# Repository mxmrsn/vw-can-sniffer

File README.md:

# VW CAN Sniffer

A home-built diagnostic interface for an MK7.5 VW GTI: hardware that plugs into the OBD-II port, firmware that
speaks the car's diagnostic protocol, and host tools for scanning modules, reading fault codes and logging live
data. The longer-term aim is an iOS app with custom dashboards talking to a low-profile dongle.

## Layout
| Path | What it is |
|---|---|
| [`hardware/pico2w/`](hardware/pico2w/README.md) | **Board v0.2.0 (tag `v0.2.0`):** Raspberry Pi Pico 2 W carrier, its firmware and bring-up plan |
| [`hardware/xiao-esp32s3/`](hardware/xiao-esp32s3/README.md) | **Current board (v0.3.0):** Seeed XIAO ESP32-S3 carrier, because the Pico 2 W is hard to buy |
| [`hardware/esp32s3-dongle/`](hardware/esp32s3-dongle/README.md) | **Next (v0.4.0), schematics drawn:** OBD dongle, two boards stacked behind a J1962 plug |
| [`hardware/teensy-esp32/`](hardware/teensy-esp32/README.md) | Original board (v0.1.0, tag `v0.1.0`): Teensy 4.0 + ESP32, its firmware and tools |
| [`tools/vwdiag/`](tools/vwdiag/README.md) | Host tools: scan, identification, fault codes, live data, logging, frame decoding |
| [`tools/tests/`](tools/tests) | End-to-end tests for the tools, run against the firmware simulator |
| [`docs/roadmap.md`](docs/roadmap.md) | **What comes next, in order**: hardware, simulator, iOS app, data, tuning |
| [`ios/`](ios/README.md) | The iOS app (SwiftUI) and its protocol package, running against the simulator |
| [`docs/logging_experiments.md`](docs/logging_experiments.md) | Scripted experiments for the car, and calibrating the simulator from them |
| [`docs/`](docs/vw_can_data_sources.md) | Project-wide notes, including where the VW-specific data came from |

Each board folder holds everything specific to that board: `pcb/` (KiCad project, BOM, fab files), `firmware/`
and `docs/`.

## Status
- **v0.2.0 board (Pico 2 W):** designed, checked by ERC/DRC and ready to order. Not yet built.
- **v0.3.0 board (XIAO ESP32-S3):** routed and DRC clean, 68 x 38 mm. A few BOM lines still need a stock
  check before ordering.
- **Firmware:** CAN, ISO-TP, UDS, a USB console, a framed binary protocol over USB and Bluetooth LE, and logging
  to a microSD card. The application core is shared by both boards. Builds for the Pico 2 W and the XIAO
  ESP32-S3; **never run on hardware.**
- **Tools:** working and tested against a simulated car, over the text console, the binary protocol and a
  Bluetooth stand-in. Nothing has been tried on the real car.

## Quick start (no hardware needed)
```bash
make -C hardware/pico2w/firmware/sim
cd tools
python3 -m vwdiag --sim --transmit scan
```

## Tests
```bash
make -C hardware/pico2w/firmware/tests
python3 -m unittest discover -s tools/tests
```

Both run on every push, along with firmware builds for every supported board ([`.github/workflows/ci.yml`](.github/workflows/ci.yml)).

## Other
- `tools/md_to_pdf.sh` regenerates the PDF copy that sits next to each Markdown write-up.

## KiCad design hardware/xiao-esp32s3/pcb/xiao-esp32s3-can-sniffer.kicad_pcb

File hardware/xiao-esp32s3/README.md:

# XIAO ESP32-S3 board (v0.3.0)

| Path | What it is |
|---|---|
| [`pcb/`](pcb/docs/README.md) | KiCad project, with the board write-up in `pcb/docs/README.md` |
| [`firmware/`](firmware/README.md) | ESP-IDF firmware: the shared core from the Pico board plus this chip's drivers |
| [`docs/design_notes.md`](docs/design_notes.md) | Why this board exists, the pin map, and what is decided |
| [`docs/bringup_plan.md`](docs/bringup_plan.md) | What to test, in order, when the boards arrive: bench, phone, car |
| [`bench-car/`](bench-car/README.md) | Firmware for a second board that answers like the car, for testing on the desk |

Same job as [`../pico2w`](../pico2w/README.md) with a module that is actually in stock, CAN as a hardware
peripheral instead of software bit-banging, and Bluetooth in the main chip. The application core, the link
protocol, the logging format and the Python tools are shared with that board.

**Nothing here has been built or run.** The schematic is complete and checked, the board is routed and DRC
clean, and the firmware compiles.

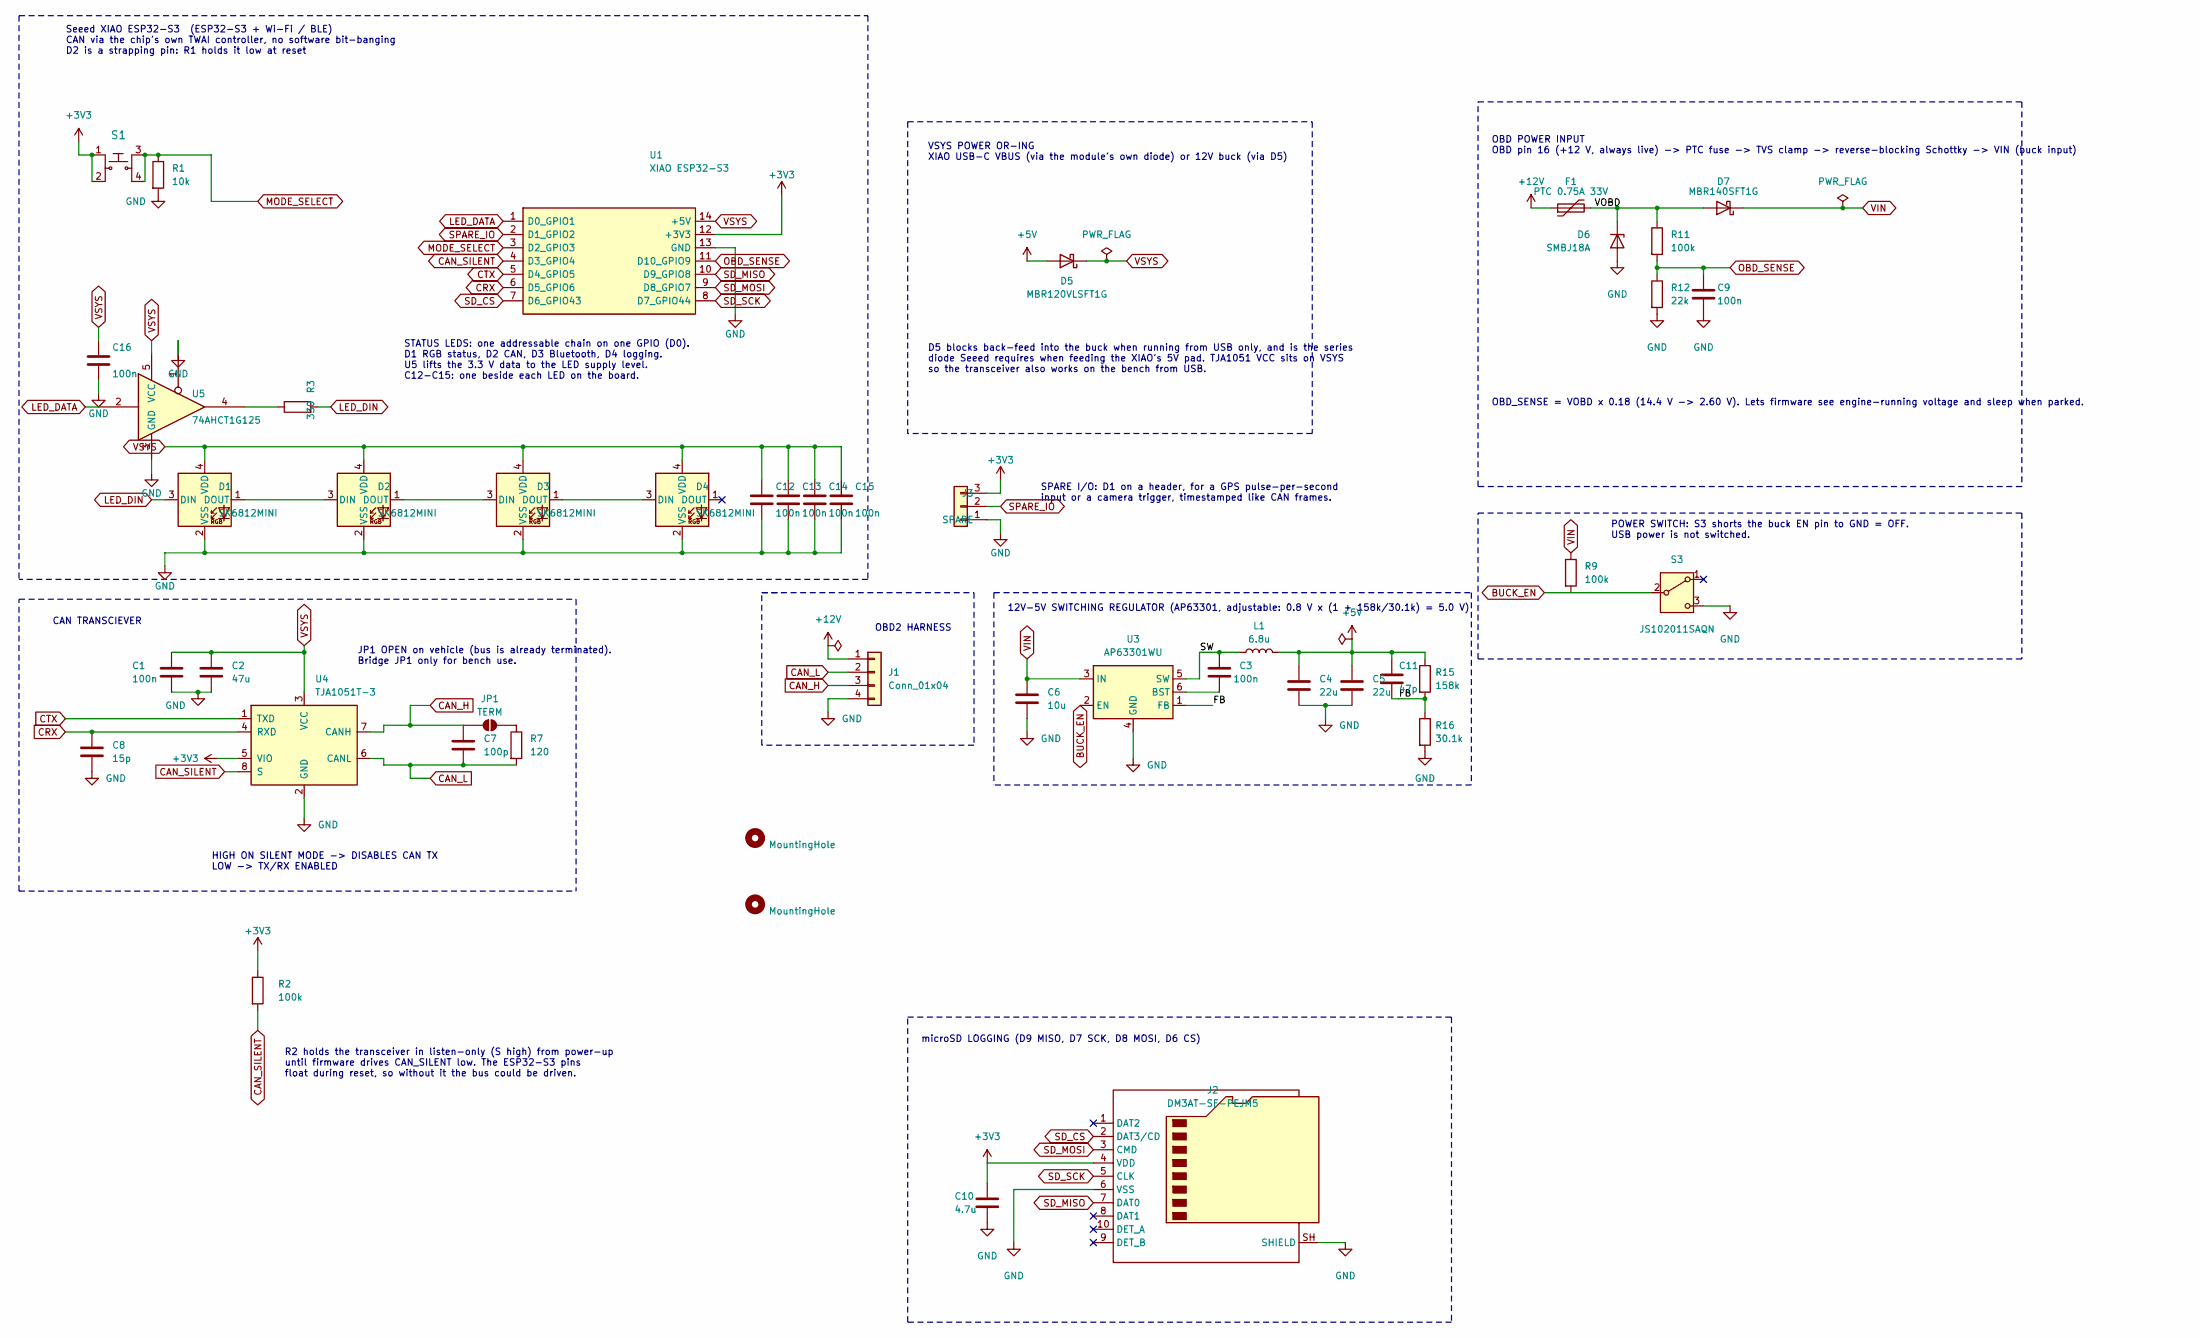
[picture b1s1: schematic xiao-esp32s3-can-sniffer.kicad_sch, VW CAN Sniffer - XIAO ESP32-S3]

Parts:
C1, C3: 100n; C_0805_2012Metric; MPN CL21B104KBCNNNC; DigiKey 1276-1003-1-ND
C2: 47u; C_0805_2012Metric; MPN CL21A476MQCLRNC; DigiKey 1276-2420-1-ND
C4, C5: 22u; C_0805_2012Metric; MPN CL21A226KOQNNNE; DigiKey 1276-6526-1-ND
C6: 10u; C_0805_2012Metric; MPN GMC21X5R106K50NT; DigiKey 4713-GMC21X5R106K50NTCT-ND
C7: 100p; C_0805_2012Metric; MPN CL21C101JBANNNC; DigiKey 1276-1014-1-ND
C8: 15p; C_0805_2012Metric; MPN CC0805JRNPO9BN150; DigiKey 311-1101-1-ND
C9, C12, C13, C14, C15, C16: 100n; C_0603_1608Metric; MPN CC0603KRX7R9BB104; DigiKey 311-1344-1-ND
C10: 4.7u; C_0603_1608Metric; MPN CC0603KRX5R7BB475; DigiKey 311-1785-1-ND
C11: 47p; C_0603_1608Metric; MPN CL10C470JB8NNNC; DigiKey 1276-1037-1-ND
D1, D2, D3, D4: SK6812MINI; LED_SK6812MINI_PLCC4_3.5x3.5mm_P1.75mm; MPN SK6812mini-012; LCSC C2886570
D5: MBR120VLSFT1G; D_SOD-123F; MPN MBR120VLSFT1G; DigiKey MBR120VLSFT1GOSCT-ND
D6: SMBJ18A; D_SMB; MPN SMBJ18A; DigiKey SMBJ18ALFCT-ND
D7: MBR140SFT1G; D_SOD-123F; MPN MBR140SFT1G; DigiKey MBR140SFT1GOSCT-ND
F1: PTC 0.75A 33V; Fuse_1812_4532Metric; MPN 1812L075/33DR; DigiKey F3355CT-ND
H1, H3: MountingHole; MountingHole_2.5mm
J1: Conn_01x04; CONN_874370231-SD_04_MOL; MPN 0874370473; DigiKey WM3969CT-ND
J2: DM3AT-SF-PEJM5; microSD_HC_Hirose_DM3AT-SF-PEJM5; MPN DM3AT-SF-PEJM5; DigiKey HR1964CT-ND
J3: SPARE; PinHeader_1x03_P2.54mm_Vertical; MPN PRPC003SAAN-RC; DigiKey S1011EC-03-ND
JP1: TERM; SolderJumper-2_P1.3mm_Open_RoundedPad1.0x1.5mm
L1: 6.8u; L_Wurth_WE-LQSH-4020; MPN 74404042068; DigiKey 732-5507-1-ND
R1: 10k; R_0603_1608Metric; MPN CRCW060310K0FKEA; DigiKey 541-10.0KHCT-ND
R2, R9, R11: 100k; R_0603_1608Metric; MPN CRCW0603100KFKEA; DigiKey 541-100KHCT-ND
R3: 330; R_0603_1608Metric; MPN CRCW0603330RFKEA; DigiKey 541-330HCT-ND
R7: 120; R_0603_1608Metric; MPN RC0603FR-07120RL; DigiKey 311-120HRCT-ND
R12: 22k; R_0603_1608Metric; MPN CRCW060322K0FKEA; DigiKey 541-22.0KHCT-ND
R15: 158k; R_0603_1608Metric; MPN CRCW0603158KFKEA; DigiKey 541-158KHCT-ND
R16: 30.1k; R_0603_1608Metric; MPN CRCW060330K1FKEA; DigiKey 541-30.1KHCT-ND
S1: PTS645SM43SMTR92_LFS; Switch_Tactile_SMD_6x6mm_PTS645; MPN PTS645SM43SMTR92 LFS; Digi-Key_PN CKN9112CT-ND
S3: JS102011SAQN; SW_SPDT_CK_JS102011SAQN; MPN JS102011SAQN; DigiKey 401-1999-1-ND
U1: XIAO ESP32-S3; Seeed_XIAO_THT; MPN 113991114
U3: AP63301WU; TSOT-23-6; MPN AP63301WU-7; DigiKey 31-AP63301WU-7CT-ND
U4: TJA1051T-3; SOIC-8_3.9x4.9mm_P1.27mm; MPN TJA1051T/3,118; DigiKey 568-8684-1-ND
U5: 74AHCT1G125; SOT-23-5; MPN SN74AHCT1G125DBVR; DigiKey 296-1180-1-ND

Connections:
+3V3: C10.1, J2.4 (VDD), J3.3, R2.1, S1.1, S1.2, U1.12 (+3V3), U4.5 (VIO)
+5V: C4.1, C5.1, C11.1, D5.2 (A), L1.2, R15.1
+12V: F1.1, J1.1
/FB: C11.2, R15.2, R16.1, U3.1 (FB)
/SW: C3.2, L1.1, U3.5 (SW)
/VOBD: D6.1 (K), D7.2 (A), F1.2, R11.1
BUCK_EN: R9.2, S3.2 (B), U3.2 (EN)
CAN_H: C7.1, J1.3, JP1.1 (A), U4.7 (CANH)
CAN_L: C7.2, J1.2, R7.2, U4.6 (CANL)
CAN_SILENT: R2.2, U1.4 (D3_GPIO4), U4.8 (S)
CRX: C8.1, U1.6 (D5_GPIO6), U4.4 (RXD)
CTX: U1.5 (D4_GPIO5), U4.1 (TXD)
GND: C1.2, C2.2, C4.2, C5.2, C6.2, C8.2, C9.2, C10.2, C12.2, C13.2, C14.2, C15.2, C16.2, D1.2 (VSS), D2.2 (VSS), D3.2 (VSS), D4.2 (VSS), D6.2 (A), J1.4, J2.6 (VSS), J2.SH (SHIELD), J3.1, R1.2, R12.2, R16.2, S3.3 (C), U1.13 (GND), U3.4 (GND), U4.2 (GND), U5.1, U5.3 (GND)
LED_DATA: U1.1 (D0_GPIO1), U5.2
LED_DIN: D1.3 (DIN), R3.2
MODE_SELECT: R1.1, S1.3, S1.4, U1.3 (D2_GPIO3)
unnamed: D1.1 (DOUT), D2.3 (DIN)
unnamed: D2.1 (DOUT), D3.3 (DIN)
unnamed: D3.1 (DOUT), D4.3 (DIN)
unnamed: JP1.2 (B), R7.1
unnamed: R3.1, U5.4
unnamed: C3.1, U3.6 (BST)
OBD_SENSE: C9.1, R11.2, R12.1, U1.11 (D10_GPIO9)
SD_CS: J2.2 (DAT3/CD), U1.7 (D6_GPIO43)
SD_MISO: J2.7 (DAT0), U1.10 (D9_GPIO8)
SD_MOSI: J2.3 (CMD), U1.9 (D8_GPIO7)
SD_SCK: J2.5 (CLK), U1.8 (D7_GPIO44)
SPARE_IO: J3.2, U1.2 (D1_GPIO2)
VIN: C6.1, D7.1 (K), R9.1, U3.3 (IN)
VSYS: C1.1, C2.1, C12.1, C13.1, C14.1, C15.1, C16.1, D1.4 (VDD), D2.4 (VDD), D3.4 (VDD), D4.4 (VDD), D5.1 (K), U1.14 (+5V), U4.3 (VCC), U5.5 (VCC)

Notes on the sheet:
Seeed XIAO ESP32-S3 (ESP32-S3 + Wi-Fi / BLE) CAN via the chip's own TWAI controller, no software bit-banging D2 is a strapping pin: R1 holds it low at reset
12V-5V SWITCHING REGULATOR (AP63301, adjustable: 0.8 V x (1 + 158k/30.1k) = 5.0 V)
CAN TRANSCIEVER
HIGH ON SILENT MODE -> DISABLES CAN TX LOW -> TX/RX ENABLED
OBD2 HARNESS
VSYS POWER OR-ING XIAO USB-C VBUS (via the module's own diode) or 12V buck (via D5)
D5 blocks back-feed into the buck when running from USB only, and is the series diode Seeed requires when feeding the XIAO's 5V pad. TJA1051 VCC sits on VSYS so the transceiver also works on the bench from USB.
JP1 OPEN on vehicle (bus is already terminated). Bridge JP1 only for bench use.
OBD POWER INPUT OBD pin 16 (+12 V, always live) -> PTC fuse -> TVS clamp -> reverse-blocking Schottky -> VIN (buck input)
OBD_SENSE = VOBD x 0.18 (14.4 V -> 2.60 V). Lets firmware see engine-running voltage and sleep when parked.
POWER SWITCH: S3 shorts the buck EN pin to GND = OFF. USB power is not switched.
microSD LOGGING (D9 MISO, D7 SCK, D8 MOSI, D6 CS)
R2 holds the transceiver in listen-only (S high) from power-up until firmware drives CAN_SILENT low. The ESP32-S3 pins float during reset, so without it the bus could be driven.
STATUS LEDS: one addressable chain on one GPIO (D0). D1 RGB status, D2 CAN, D3 Bluetooth, D4 logging. U5 lifts the 3.3 V data to the LED supply level. C12-C15: one beside each LED on the board.
SPARE I/O: D1 on a header, for a GPS pulse-per-second input or a camera trigger, timestamped like CAN frames.

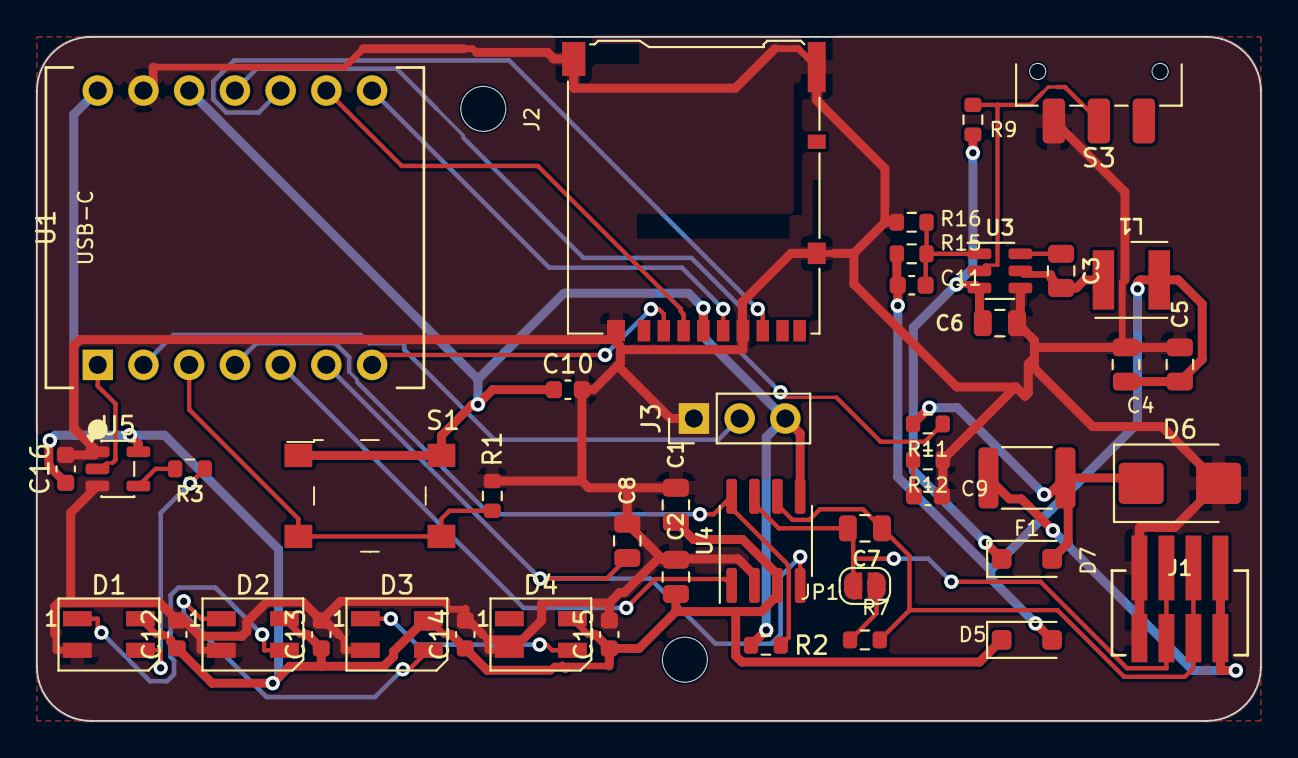
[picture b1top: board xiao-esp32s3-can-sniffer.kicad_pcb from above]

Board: 2 copper layers, 68.0 x 38.0 mm, 46 parts (0 on the bottom side), 30 nets.

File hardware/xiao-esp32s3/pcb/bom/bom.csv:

Refs,Qty,Value,Description,Manufacturer,MPN,DigiKey PN,DigiKey stock (2026-11-15),Unit price USD (qty 1),Stock checked,Notes
"C1,C3",2,100n,Cap cer 0.1uF 50V X7R 0805,Samsung Electro-Mechanics,CL21B104KBCNNNC,1276-1003-1-ND,"3,797,498",0.10,yes (2026-11-15),
C2,1,47u,Cap cer 47uF 6.3V X5R 0805,Samsung Electro-Mechanics,CL21A476MQCLRNC,1276-2420-1-ND,"6,613",0.53,yes (2026-11-15),6.3 V part on the ~5 V VSYS rail; 10 V versions were all out of stock
"C4,C5",2,22u,Cap cer 22uF 16V X5R 0805,Samsung Electro-Mechanics,CL21A226KOQNNNE,1276-6526-1-ND,"95,660",0.42,yes (2026-11-15),Buck output
C6,1,10u,Cap cer 10uF 50V X5R 0805,Cal-Chip Electronics,GMC21X5R106K50NT,4713-GMC21X5R106K50NTCT-ND,"15,332",1.76,yes (2026-11-15),Buck input; 50 V for OBD transients. Only in-stock 50 V option
C7,1,100p,Cap cer 100pF 50V C0G 0805,Samsung Electro-Mechanics,CL21C101JBANNNC,1276-1014-1-ND,"127,138",0.10,yes (2026-11-15),
C8,1,15p,Cap cer 15pF 50V C0G 0805,YAGEO,CC0805JRNPO9BN150,311-1101-1-ND,"31,676",,yes (2026-11-15),
"C9,C12,C13,C14,C15,C16",6,100n,Cap cer 0.1uF 50V X7R 0603,YAGEO,CC0603KRX7R9BB104,311-1344-1-ND,"3,118,948",,yes (2026-11-15),
C10,1,4.7u,Cap cer 4.7uF 16V X5R 0603,YAGEO,CC0603KRX5R7BB475,311-1785-1-ND,"125,573",,yes (2026-11-15),
C11,1,47p,Cap cer 47pF 50V C0G 0603,Samsung Electro-Mechanics,CL10C470JB8NNNC,1276-1037-1-ND,"1,223,201",,yes (2026-11-15),Feed-forward capacitor
"D1,D2,D3,D4",4,SK6812MINI,"Addressable RGB LED 3.5x3.5 mm, SK6812MINI or equivalent",Opsco,SK6812mini-012,,,0.10 (LCSC),"yes (2026-11-15, LCSC C2886570: 34,385)","Matches the KiCad SK6812MINI footprint corner for corner (DOUT, VDD, DIN, GND; chamfer at DIN). Do NOT substitute SK6812MINI-HS or -E: their pinouts differ. Not found at DigiKey; order from LCSC or have the assembler source it"
D5,1,MBR120VLSFT1G,Schottky 20V 1A SOD-123FL,onsemi,MBR120VLSFT1G,MBR120VLSFT1GOSCT-ND,"105,067",0.61,yes (2026-11-15),
D6,1,SMBJ18A,TVS 18V 29.2Vc unidirectional SMB,Littelfuse,SMBJ18A,SMBJ18ALFCT-ND,"26,211",,yes (2026-11-15),
D7,1,MBR140SFT1G,Schottky 40V 1A SOD-123FL,onsemi,MBR140SFT1G,MBR140SFT1GOSCT-ND,"49,072",0.60,yes (2026-11-15),
F1,1,PTC 0.75A 33V,PTC resettable fuse 33V 750mA 1812,Littelfuse,1812L075/33DR,F3355CT-ND,"18,996",,yes (2026-11-15),
J1,1,Conn_01x04,Header 4 pos 1.5mm vertical SMD,Molex,0874370473,WM3969CT-ND,"18,264",0.94,yes (2026-11-15),Mating housing and crimps not included
J2,1,DM3AT-SF-PEJM5,microSD push-push socket,Hirose,DM3AT-SF-PEJM5,HR1964CT-ND,"72,391",3.55,yes (2026-11-15),
J3,1,SPARE,Header 1x3 2.54 mm vertical,Sullins,PRPC003SAAN-RC,S1011EC-03-ND,,,generic (any 1x3 2.54 mm header),Spare GPIO (D1) for a GPS pulse-per-second input or a camera sync line
JP1,1,TERM,,,,,,,n/a,"Solder jumper on the PCB, nothing to buy. Bridge it only for bench use"
L1,1,6.8u,Inductor 6.8uH 1.45A 4x4x1.8mm WE-LQS 4020,Wurth Elektronik,74404042068,732-5507-1-ND,88,1.16,yes (2026-11-15),Low stock. Check the land pattern against the footprint before ordering
R1,1,10k,Res 10k 1% 1/10W 0603,Vishay Dale,CRCW060310K0FKEA,541-10.0KHCT-ND,"2,848,541",,yes (2026-11-15),
"R2,R9,R11",3,100k,Res 100k 1% 1/10W 0603,Vishay Dale,CRCW0603100KFKEA,541-100KHCT-ND,"2,913,990",,yes (2026-11-15),Holds the transceiver in listen-only until firmware drives it low
R3,1,330,Res 330R 1% 1/10W 0603,Vishay Dale,CRCW0603330RFKEA,541-330HCT-ND,"313,586",,yes (2026-11-15),"Series resistor on the LED data line, damps ringing"
R7,1,120,Res 120R 1% 1/10W 0603,YAGEO,RC0603FR-07120RL,311-120HRCT-ND,"4,590",0.10,yes (2026-11-15),
R12,1,22k,Res 22k 1% 1/10W 0603,Vishay Dale,CRCW060322K0FKEA,541-22.0KHCT-ND,"282,701",,yes (2026-11-15),
R15,1,158k,Res 158k 1% 1/10W 0603,Vishay Dale,CRCW0603158KFKEA,541-158KHCT-ND,"20,675",,yes (2026-11-15),"Feedback divider, top"
R16,1,30.1k,Res 30.1k 1% 1/10W 0603,Vishay Dale,CRCW060330K1FKEA,541-30.1KHCT-ND,"90,123",,yes (2026-11-15),"Feedback divider, bottom"
S1,1,PTS645SM43SMTR92_LFS,Tactile switch 6x6mm SMD,C&K,PTS645SM43SMTR92 LFS,CKN9112CT-ND,"127,640",,yes (2026-11-15),
S3,1,JS102011SAQN,Slide switch SPDT right-angle SMD,C&K,JS102011SAQN,401-1999-1-ND,"52,303",0.90,yes (2026-11-15),
U1,1,XIAO ESP32-S3,Seeed XIAO ESP32-S3 module (not Sense),Seeed Studio,113991114,1597-113991114-ND,,7.99 (Seeed),"yes (2026-11-15, Seeed store: in stock)","Seeed XIAO ESP32-S3 (not Sense). Socket on 2x 1x7 2.54mm headers, or solder the module flat. Footprint rows corrected to 15.24 mm on 2026-11-15, checked against Seeed's official KiCad footprint."
U3,1,AP63301WU,Buck regulator adjustable 3A TSOT-26,Diodes Incorporated,AP63301WU-7,31-AP63301WU-7CT-ND,156,0.96,yes (2026-11-15),"Low stock. Automotive AP63301QWU-7 (31-AP63301QWU-7CT-ND, 815 in stock) is a drop-in"
U4,1,TJA1051T-3,CAN transceiver SO-8 with VIO,NXP,"TJA1051T/3,118",568-8684-1-ND,"12,998",,yes (2026-11-15),
U5,1,74AHCT1G125,"Single buffer, TTL-level input, SOT-23-5",Texas Instruments,SN74AHCT1G125DBVR,296-1180-1-ND,,0.14,"yes (2026-11-15, DigiKey lists it; LCSC C7484: 33,071)",Lifts the 3.3 V LED data line to the LEDs supply level (their input threshold is 0.7 x VDD)
--,4,Socket strip,"Socket 1x7 2.54mm, on the board for the module",Sullins,PPTC071LFBN-RC,S7036-ND,,,generic (any 1x7 2.54 mm female header),Not on schematic. Two per board; order spares. Or solder the module flat
--,4,Pin header,"Header 1x7 2.54mm, soldered to the module",Sullins,PRPC007SAAN-RC,S1011EC-07-ND,,,generic (any 1x7 2.54 mm male header; Seeed ships some XIAOs with headers),Not on schematic. The XIAO ships without headers

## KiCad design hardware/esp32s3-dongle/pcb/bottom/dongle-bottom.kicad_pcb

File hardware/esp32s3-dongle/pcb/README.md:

# OBD dongle boards (v0.4.0)

| Path | What it is |
|---|---|
| `bottom/dongle-bottom.kicad_sch` | J1962 plug, protection, TJA1043T CAN with sleep and wake, INH-switched 5 V buck, wake detector |
| `top/dongle-top.kicad_sch` | ESP32-S3-MINI-1, USB-C, 3.3 V, microSD, LED chain, button, IMU (optional), GPS / sync and expansion |
| `lib/dongle.kicad_sym` | Symbols KiCad does not ship (TPS3700) |
| `bottom/dongle-bottom.kicad_pcb`, `top/dongle-top.kicad_pcb` | Both boards, placed and routed on a temporary 56 x 44 mm outline, 0 DRC errors |
| `step/` | Both boards as STEP, every part modelled, for the enclosure |
| `3dmodels/` | Placeholder boxes for parts KiCad has no model for (`make_models.py`) |
| `scripts/` | Generators for both schematics (`sheetgen.py` turns a parts list into a label-connected sheet), placement (`layout.py`), and the whole pipeline (`route.sh`) |

The outline is a stand-in until the enclosure exists; the plug is held by the enclosure and wired to pads on the
bottom board. See [`../docs/architecture.md`](../docs/architecture.md).

```bash
hardware/esp32s3-dongle/pcb/scripts/route.sh    # schematics, netlists, placement, autorouting, DRC, STEP, renders
```

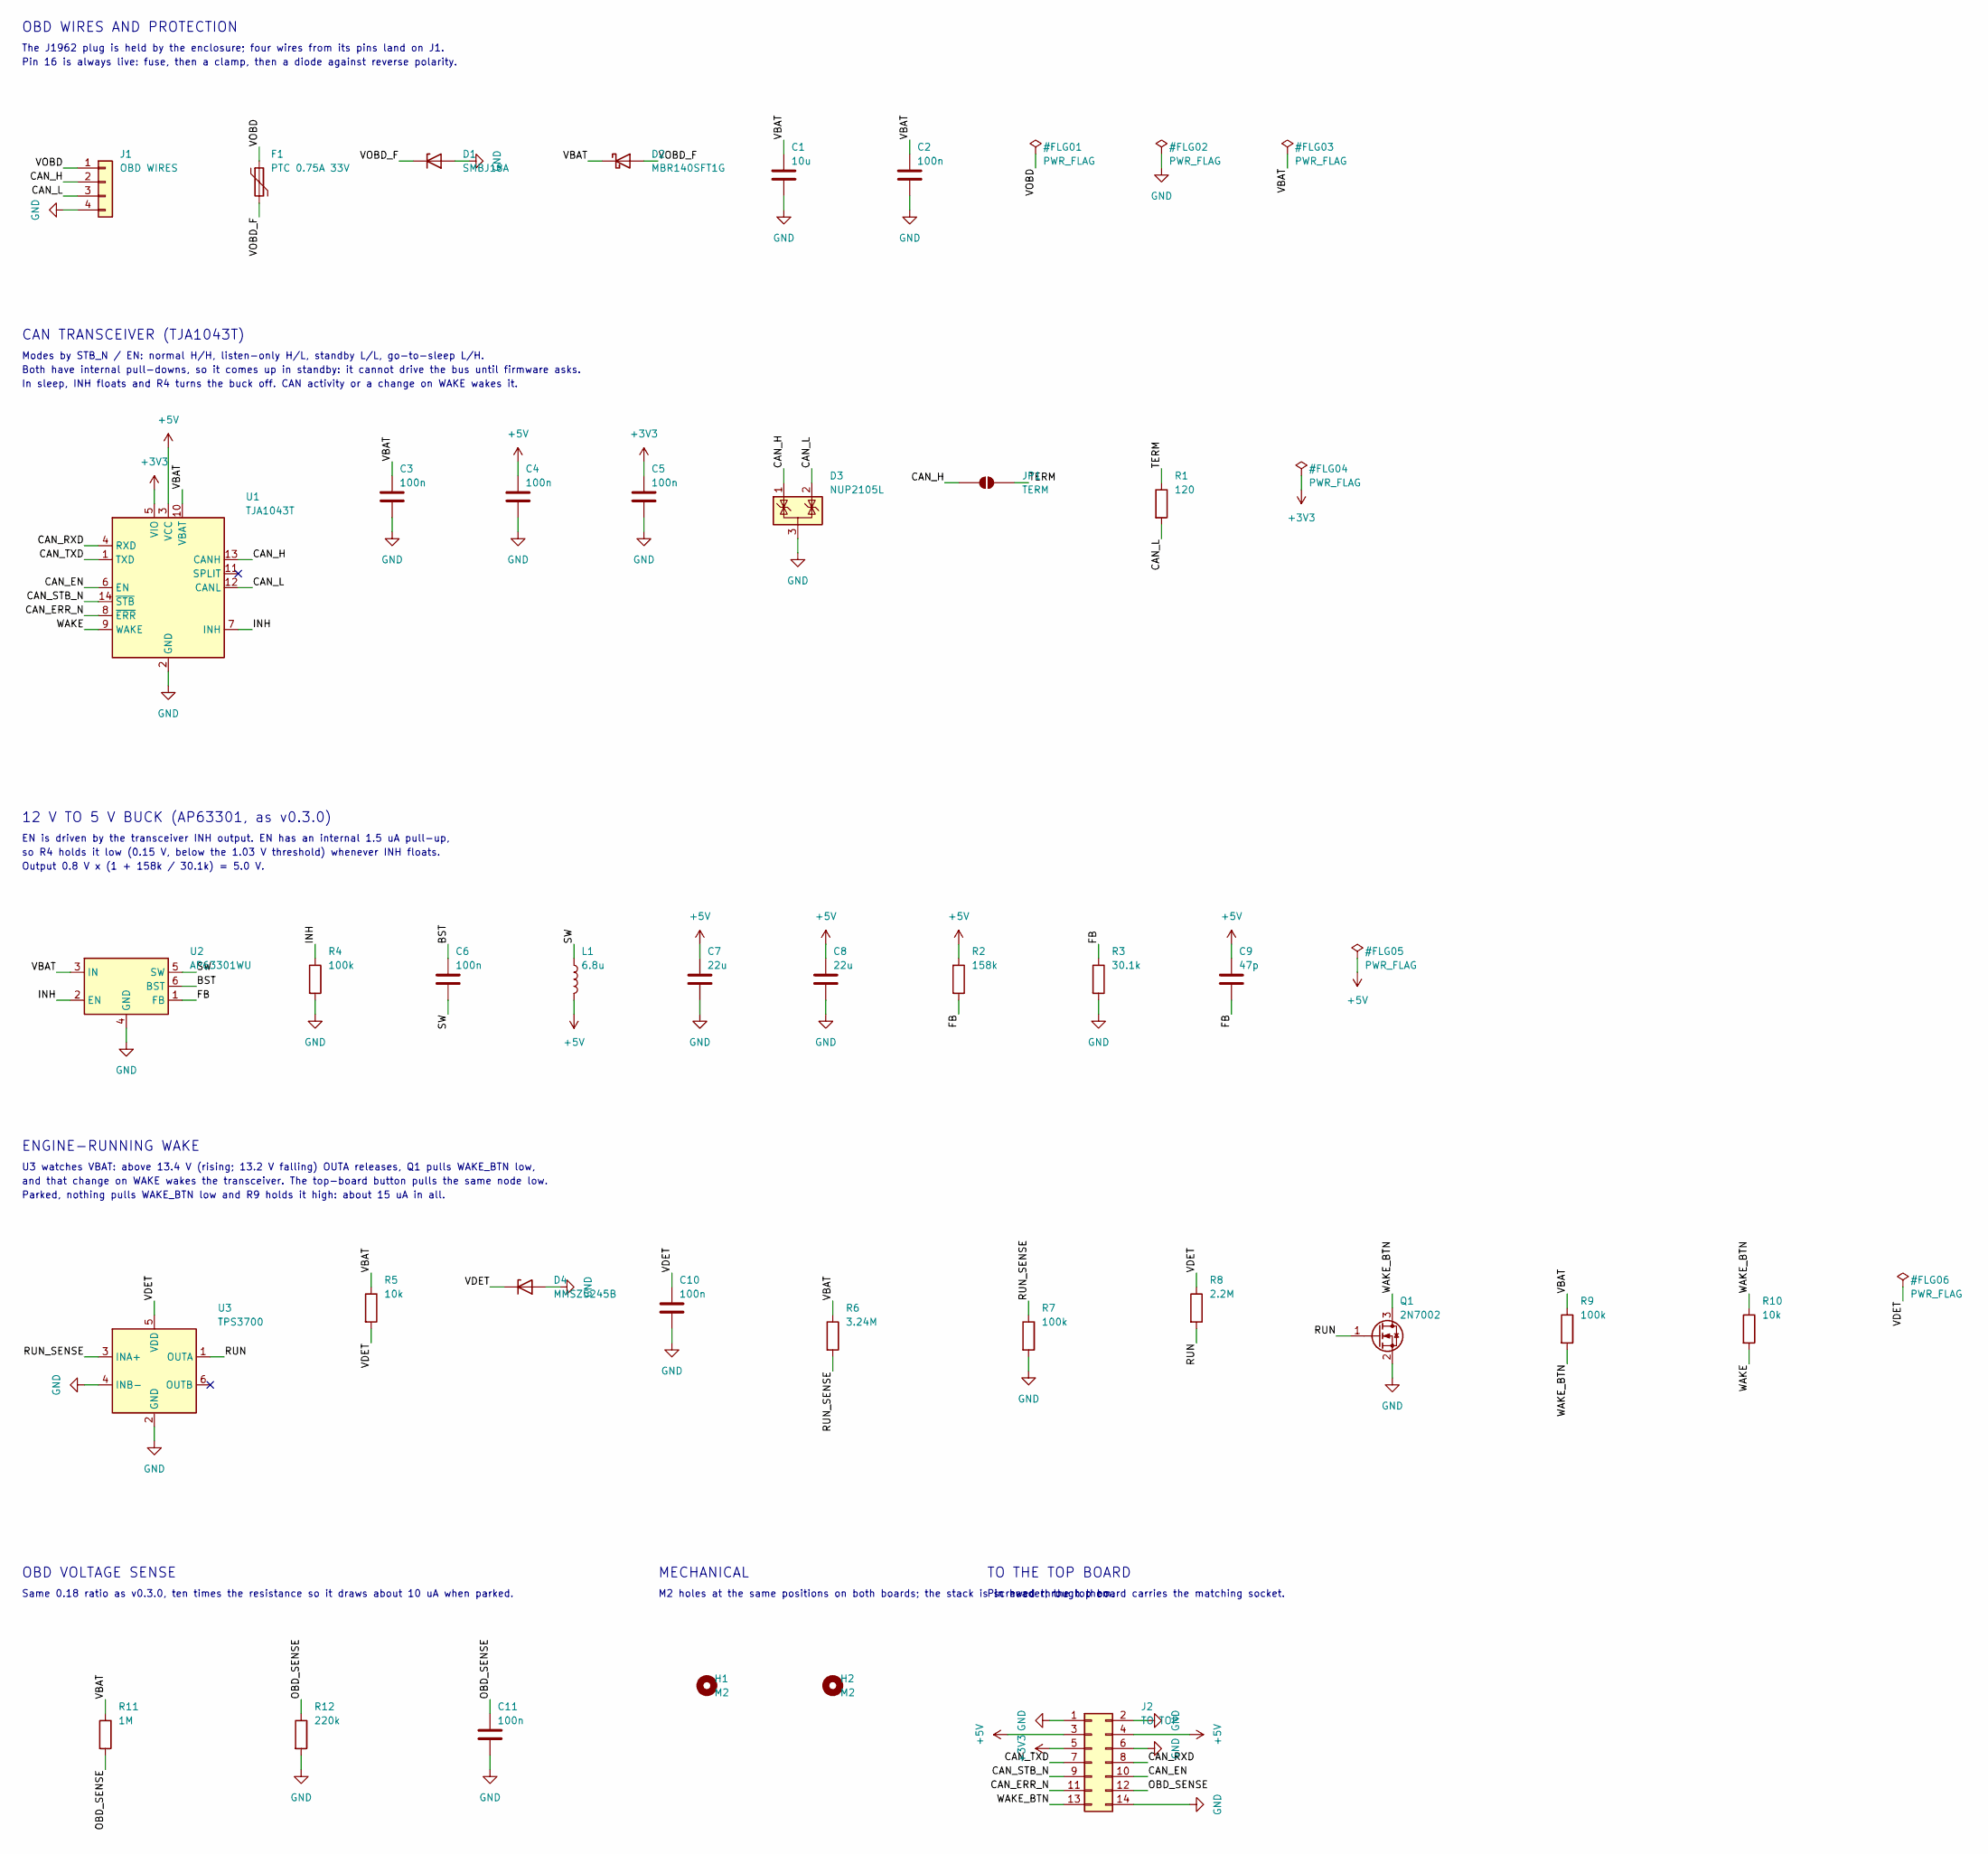
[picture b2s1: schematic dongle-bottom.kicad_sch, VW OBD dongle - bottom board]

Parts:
C1: 10u; C_0805_2012Metric; MPN GMC21X5R106K50NT; DigiKey 4713-GMC21X5R106K50NTCT-ND
C2, C3, C6: 100n; C_0805_2012Metric; MPN CL21B104KBCNNNC; DigiKey 1276-1003-1-ND
C4, C5, C10, C11: 100n; C_0603_1608Metric; MPN CC0603KRX7R9BB104; DigiKey 311-1344-1-ND
C7, C8: 22u; C_0805_2012Metric; MPN CL21A226KOQNNNE; DigiKey 1276-6526-1-ND
C9: 47p; C_0603_1608Metric; MPN CL10C470JB8NNNC; DigiKey 1276-1037-1-ND
D1: SMBJ18A; D_SMB; MPN SMBJ18A; DigiKey SMBJ18ALFCT-ND
D2: MBR140SFT1G; D_SOD-123F; MPN MBR140SFT1G; DigiKey MBR140SFT1GOSCT-ND
D3: NUP2105L; SOT-23; MPN NUP2105LT1G
D4: MMSZ5245B; D_SOD-123; MPN MMSZ5245BT1G
F1: PTC 0.75A 33V; Fuse_1812_4532Metric; MPN 1812L075/33DR; DigiKey F3355CT-ND
H1, H2: M2; MountingHole_2.2mm_M2
J1: OBD WIRES; SolderWire-0.25sqmm_1x04_P4.2mm_D0.65mm_OD1.7mm_Relief2x
J2: TO TOP; PinHeader_2x07_P1.27mm_Vertical_SMD
JP1: TERM; SolderJumper-2_P1.3mm_Open_RoundedPad1.0x1.5mm
L1: 6.8u; L_Wurth_WE-LQSH-4020; MPN 74404042068; DigiKey 732-5507-1-ND
Q1: 2N7002; SOT-23; MPN 2N7002
R1: 120; R_0603_1608Metric; MPN RC0603FR-07120RL; DigiKey 311-120HRCT-ND
R2: 158k; R_0603_1608Metric; MPN CRCW0603158KFKEA; DigiKey 541-158KHCT-ND
R3: 30.1k; R_0603_1608Metric; MPN CRCW060330K1FKEA; DigiKey 541-30.1KHCT-ND
R4, R7, R9: 100k; R_0603_1608Metric; MPN CRCW0603100KFKEA; DigiKey 541-100KHCT-ND
R5, R10: 10k; R_0603_1608Metric; MPN CRCW060310K0FKEA; DigiKey 541-10.0KHCT-ND
R6: 3.24M; R_0603_1608Metric; MPN CRCW06033M24FKEA
R8: 2.2M; R_0603_1608Metric; MPN CRCW06032M20FKEA
R11: 1M; R_0603_1608Metric; MPN CRCW06031M00FKEA
R12: 220k; R_0603_1608Metric; MPN CRCW0603220KFKEA
U1: TJA1043T; SOIC-14_3.9x8.7mm_P1.27mm; MPN TJA1043T/1J
U2: AP63301WU; TSOT-23-6; MPN AP63301WU-7; DigiKey 31-AP63301WU-7CT-ND
U3: TPS3700; SOT-23-6; MPN TPS3700DDCR

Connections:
+3V3: C5.1, J2.5, U1.5 (VIO)
+5V: C4.1, C7.1, C8.1, C9.1, J2.3, J2.4, L1.2, R2.1, U1.3 (VCC)
/BST: C6.1, U2.6 (BST)
/CAN_EN: J2.10, U1.6 (EN)
/CAN_ERR_N: J2.11, U1.8 (~ERR)
/CAN_H: D3.1 (K), J1.2, JP1.1 (A), U1.13 (CANH)
/CAN_L: D3.2 (K), J1.3, R1.2, U1.12 (CANL)
/CAN_RXD: J2.8, U1.4 (RXD)
/CAN_STB_N: J2.9, U1.14 (~STB)
/CAN_TXD: J2.7, U1.1 (TXD)
/FB: C9.2, R2.2, R3.1, U2.1 (FB)
/INH: R4.1, U1.7 (INH), U2.2 (EN)
/OBD_SENSE: C11.1, J2.12, R11.2, R12.1
/RUN: Q1.1 (G), R8.2, U3.1 (OUTA)
/RUN_SENSE: R6.2, R7.1, U3.3 (INA+)
/SW: C6.2, L1.1, U2.5 (SW)
/TERM: JP1.2 (B), R1.1
/VBAT: C1.1, C2.1, C3.1, D2.1 (K), R5.1, R6.1, R9.1, R11.1, U1.10 (VBAT), U2.3 (IN)
/VDET: C10.1, D4.1 (K), R5.2, R8.1, U3.5 (VDD)
/VOBD: F1.1, J1.1
/VOBD_F: D1.1 (K), D2.2 (A), F1.2
/WAKE: R10.2, U1.9 (WAKE)
/WAKE_BTN: J2.13, Q1.3 (D), R9.2, R10.1
GND: C1.2, C2.2, C3.2, C4.2, C5.2, C7.2, C8.2, C10.2, C11.2, D1.2 (A), D3.3 (A), D4.2 (A), J1.4, J2.1, J2.2, J2.6, J2.14, Q1.2 (S), R3.2, R4.2, R7.2, R12.2, U1.2 (GND), U2.4 (GND), U3.2 (GND), U3.4 (INB-)

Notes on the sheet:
OBD WIRES AND PROTECTION
The J1962 plug is held by the enclosure; four wires from its pins land on J1.
Pin 16 is always live: fuse, then a clamp, then a diode against reverse polarity.
CAN TRANSCEIVER (TJA1043T)
Modes by STB_N / EN: normal H/H, listen-only H/L, standby L/L, go-to-sleep L/H.
Both have internal pull-downs, so it comes up in standby: it cannot drive the bus until firmware asks.
In sleep, INH floats and R4 turns the buck off. CAN activity or a change on WAKE wakes it.
12 V TO 5 V BUCK (AP63301, as v0.3.0)
EN is driven by the transceiver INH output. EN has an internal 1.5 uA pull-up,
so R4 holds it low (0.15 V, below the 1.03 V threshold) whenever INH floats.
Output 0.8 V x (1 + 158k / 30.1k) = 5.0 V.
ENGINE-RUNNING WAKE
U3 watches VBAT: above 13.4 V (rising; 13.2 V falling) OUTA releases, Q1 pulls WAKE_BTN low,
and that change on WAKE wakes the transceiver. The top-board button pulls the same node low.
Parked, nothing pulls WAKE_BTN low and R9 holds it high: about 15 uA in all.
OBD VOLTAGE SENSE
Same 0.18 ratio as v0.3.0, ten times the resistance so it draws about 10 uA when parked.
MECHANICAL
M2 holes at the same positions on both boards; the stack is screwed through them.
TO THE TOP BOARD
Pin header; the top board carries the matching socket.

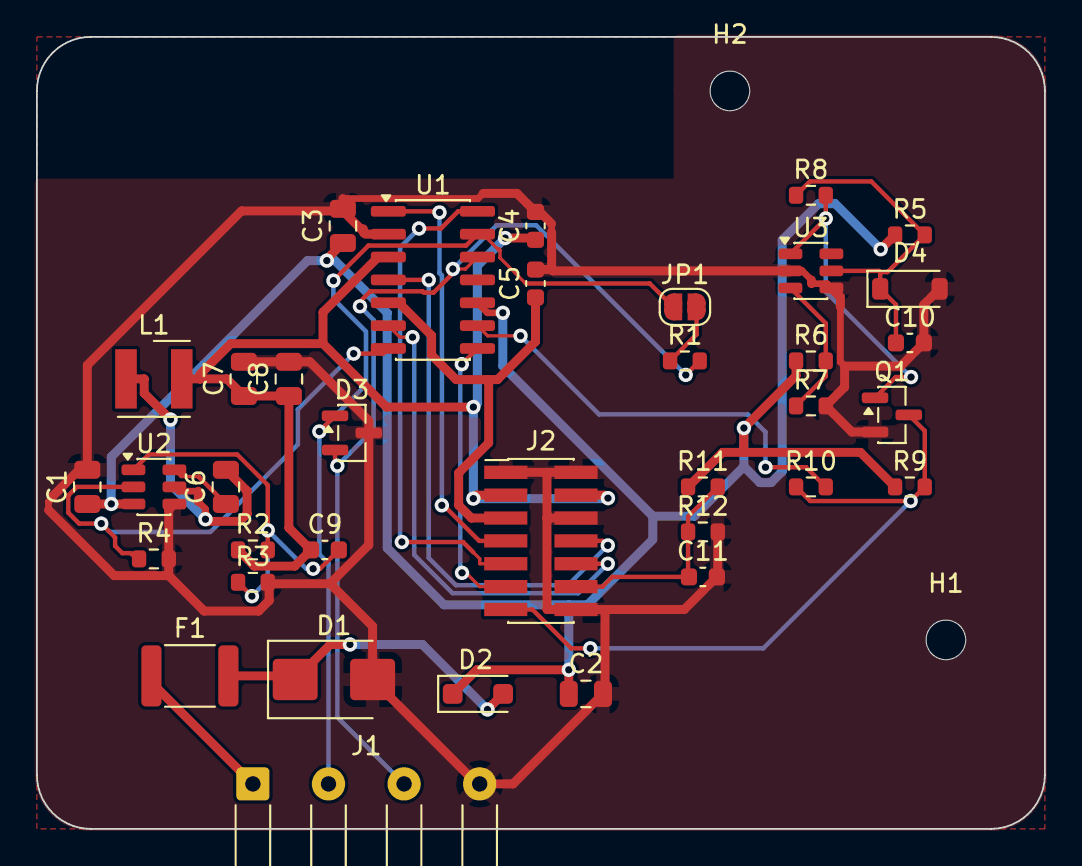
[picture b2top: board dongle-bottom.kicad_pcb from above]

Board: 2 copper layers, 56.0 x 44.0 mm, 38 parts (0 on the bottom side), 24 nets.

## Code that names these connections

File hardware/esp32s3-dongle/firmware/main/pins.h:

#pragma once

// Pin map for the OBD dongle, top board v0.4.0 (hardware/esp32s3-dongle/pcb/top): ESP32-S3-MINI-1
// GPIO numbers. Authoritative source: ../../docs/architecture.md and the schematic generator
// pcb/scripts/top.py. Signals to the bottom board go through the 2 x 7 stacking connector.

// CAN: TJA1043T on the bottom board
#define CAN_TX_PIN 4       // CAN_TXD
#define CAN_RX_PIN 5       // CAN_RXD
#define CAN_STB_N_PIN 6    // CAN_STB_N: with EN, the transceiver's mode (internal pull-down)
#define CAN_EN_PIN 7       // CAN_EN (internal pull-down)
#define CAN_ERR_N_PIN 15   // CAN_ERR_N: error, power-on and wake-source flags, active low

// Battery at the OBD port, through 1 M / 220 k on the bottom board: ADC1 channel 0.
#define OBD_SENSE_PIN 1
#define OBD_SENSE_ADC_CH ADC_CHANNEL_0
#define OBD_SENSE_RATIO ((1000.0 + 220.0) / 220.0)

// MODE button: pulls WAKE_BTN low (waking a sleeping dongle); read here through a diode, with the
// internal pull-up, so pressed reads low. The engine-running detector pulls the same node low,
// so while the engine runs the button cannot be told apart: press it with the engine off.
#define BTN_MODE_PIN 2     // MODE_IN
#define BTN_MODE_PRESSED 0
#define BTN_MODE_PULL GPIO_PULLUP_ONLY

// Four addressable LEDs in one chain, through a buffer (as on the XIAO board).
#define LED_DATA_PIN 48

// microSD, SPI mode, 47 k pull-ups on CS, MOSI and MISO.
#define SD_SPI_HOST SPI2_HOST
#define SD_CS_PIN 10
#define SD_MOSI_PIN 11
#define SD_SCK_PIN 12
#define SD_MISO_PIN 13

// GPS / sync connector (gnss_esp32.c): the receiver's UART (RXD here is the receiver's TX), its
// pulse-per-second input, and the sync output for a camera or IMU rig.
#define GPS_RXD_PIN 17
#define GPS_TXD_PIN 18
#define GPS_PPS_PIN 34
#define SYNC_OUT_PIN 35

// Not used by the firmware yet: IMU (I2C, optional part), expansion.
#define IMU_SDA_PIN 8
#define IMU_SCL_PIN 9
#define IMU_INT_PIN 16
#define EXP_CS1_PIN 14
#define EXP_CS2_PIN 21
#define EXP_INT1_PIN 47
#define EXP_INT2_PIN 33

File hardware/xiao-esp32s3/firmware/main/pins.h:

#pragma once

// Pin map for the Seeed XIAO ESP32-S3 carrier, PCB v0.3.0
// (hardware/xiao-esp32s3/pcb). GPIO numbers, not pad names; the pad each one
// sits on is in the comment. Authoritative source: ../../docs/design_notes.md.
//
// The assignment follows the board layout: signals that leave the module
// towards the transceiver, the card socket and the divider sit on the pads
// nearest them, and the two indicators and the button sit on the far side.

// CAN (TWAI) -> TJA1051T/3
#define CAN_TX_PIN 5      // D4, CTX
#define CAN_RX_PIN 6      // D5, CRX
#define CAN_SILENT_PIN 4  // D3, S: high = listen-only. R2 holds it high until this pin drives it.

// Indicators: four addressable RGB LEDs in one chain, through a buffer that
// lifts the 3.3 V data line to the LEDs' supply level. See leds.c.
#define LED_DATA_PIN 1    // D0

// Spare pad on header J3, for a GPS pulse-per-second input or a camera sync line.
#define SPARE_IO_PIN 2    // D1

// Button to +3V3 with a 10k pull-down on the board, so PRESSED = HIGH, the same
// as the v0.2.0 board. GPIO3 is a strapping pin, and the pull-down also gives it
// a defined level at reset.
#define BTN_MODE_PIN 3    // D2
#define BTN_MODE_PRESSED 1              // pressed reads high
#define BTN_MODE_PULL GPIO_FLOATING     // the board's 10k pull-down does it

// microSD, SPI mode. No external pull-up on CS: drive it high before mounting.
// GPIO43/44 are UART0 during the ROM boot log, before app_main takes them over.
#define SD_SPI_HOST SPI2_HOST
#define SD_CS_PIN 43      // D6
#define SD_SCK_PIN 44     // D7
#define SD_MOSI_PIN 7     // D8
#define SD_MISO_PIN 8     // D9

// OBD supply sense: fused OBD +12V -> 100k / 22k -> GPIO9 (ADC1_CH8).
// Reads ~0 V when powered from USB only. Read by the self-test (main.c).
#define OBD_SENSE_PIN 9   // D10
#define OBD_SENSE_ADC_CH ADC_CHANNEL_8

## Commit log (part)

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2026-02-28 Initial CAN sniffer scaffolding
2026-02-28 Add README and Teensy setup guide
2026-02-28 Serve ESP32 UI from SPIFFS
2026-02-28 Add PlatformIO SPIFFS upload script
2026-02-28 Add ESP32 upload scripts
2026-02-28 Add ESP32 heartbeat and stats
2026-02-28 Recommend TJA1051 transceiver
2026-02-28 Add Teensy CAN simulator
2026-02-28 Add TJA1051 wiring notes
2026-02-28 Document Teensy 4.1 CAN pins
2026-02-28 Add CAN1 wiring table
2026-02-28 Add system block diagram
2026-02-28 Improve dashboard with filters and stats
2026-02-28 Add Teensy-controlled ESP32 reset
2026-02-28 Add Teensy control of ESP32 RST
2026-02-28 Pulse ESP32 RST on boot
2026-02-28 Add CAN silent mode control
2026-02-28 Add Teensy heartbeat LED
2026-03-01 Add gitignore for PCB artifacts
2026-03-01 Ignore and untrack KiCad backups
2026-03-01 Add Teensy output mode switch and LEDs
2026-03-01 Add PCB doc with screenshots
2026-03-01 Link PCB docs in README
2026-03-01 Blink Wi-Fi LED in UART mode
2026-03-01 Add Teensy pins header and status frames
2026-03-01 Add status frames to dashboard and USB dump tool
2026-03-01 Document USB capture and stats
2026-03-01 Add wiring overview diagram
2026-03-01 Add UI control commands and state frames
2026-03-01 Add UI preview script
2026-03-01 Add mock data mode for UI preview
2026-03-01 Add UI labels and update PCB assets
2026-03-01 Enhance UI labeling
2026-03-01 Relocate labels card
2026-03-01 Reflow dashboard columns
2026-03-01 Fix labels render bug
2026-03-01 Fix filter interaction
2026-03-01 Make filters re-render immediately
2026-03-01 Add inline chart
2026-03-01 Add selectable plot targets
2026-03-01 Fix chart declaration
2026-03-01 Polish chart dropdowns
2026-03-01 Stabilize chart label selection
2026-03-01 Clear chart on target change
2026-03-01 Reset other dropdown on selection
2026-03-01 Add axis and grid to chart
2026-03-01 Add byte dropdown for plot
2026-03-01 Make chart collapsible
2026-03-01 Make chart hide/show
